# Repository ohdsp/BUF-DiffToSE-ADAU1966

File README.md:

# [Open Hardware DSP Platform](http://www.ohdsp.org)
## Differential to single ended buffer for ADAU1966 DAC
### Revision 1.1
###### BUF-DiffToSE-ADAU1966 (KiCad 4.0.2-stable)
---
# README
### Disclaimer
Copyright Paul Janicki 2016

Licensed under the TAPR Open Hardware License (www.tapr.org/OHL)

This documentation is distributed WITHOUT ANY EXPRESS OR IMPLIED WARRANTY, INCLUDING OF MERCHANTABILITY, SATISFACTORY QUALITY AND FITNESS FOR A PARTICULAR PURPOSE.

### What is this repository? ###

**Quick summary**

This is a differential to single ended active buffer for the ADAU1966 DAC. This is designed as part the Open Hardware DSP Platform. This may or may not be suitable for use in other applications. 

This repository contains the KiCad design files, manufacturing Gerber/drill files, and PDF/drawing files for this board.

### What is the project folder structure?
Most folder names are self explanatory. Starting from the top level: \
*BUF-DiffToSE-ADAU1966*
+ *Bill of Materials*  - This contains the bill of materials in CVS, LibreOffice Calc and XML formats
+ *Drawings*
    + *PCB* - This contains SVG and PDF outputs of PCB copper layers and assembly drawings
    + *Schematics* - This contains the PDF schematic drawing
+ *Gerbers* - This contains the PCB Gerbers and drill drawings for manufacture, there is also a zip file ready to send to most manufacturers
+ *KiCad* - This contains the original KiCad schematic and PCB design files

### How do I get set up? ###

**Summary of set up**

1. Set your self up a directory on a local disk, something simple will make life easier (eg C:\Electronics on Windows as used here), but anywhere will do just fine.
2. Download the Kicad-Libs from [https://github.com/ohdsp/KiCad-Libs](https://github.com/ohdsp/KiCad-Libs) and place in C:\Electronics\Kicad-Libs (or your chosen folder) 
3. Create a OHDSP subdirectory in C:\Electronics (so C:\Electronics\OHDSP)
3. Download this project to C:\Electronics\OHDSP\BUF-DiffToSE-ADAU1966
4. Fire up Kicad
5. Open the main project file C:\Electronics\OHDSP\BUF-DiffToSE-ADAU1966\Schematics\BUF-DiffToSE-ADAU1966.pro
6. (Optional) Setup Pcbnew component library as below.
7. Do as you wish with the project, just keep it under the TAPR Open Hardware License.

Make sure your git setup doesn't exclude files used in the project (like .LIB files) or things may go wrong down the line.

**KiCad Library Configuration**

Note that you need to setup a Pcbnew library, but the eeschema libraries should work without any changes if you followed the instructions above.

To setup Pcbnew libraries:

In Pcbnew go to Preferences -> Footprint Libraries Manager. Under Global Libraries tab in the top list check if there is a nickname "MyKiCadLibs-Footprints" (usually at the end of the list). If there is but it points to the wrong place then change the Library Path to point to MyKiCadLibs-Footprints (eg C:\Electronics\KiCad-Libs\MyKiCadLibs-Footprints.pretty) folder for your setup. If this is missing you can use "Append with Wizard", choose "Files on my computer", click next, browse to library location (eg C:\Electronics\KiCad-Libs\MyKiCadLibs-Footprints.pretty) and select the folder MyKiCadLibs-Footprints.pretty, click next, check the Status column states OK and the Format is KiCad (if not re-download the library) and click next, then select "To global library configuration..." and click Finish.

To setup eeschema component libraries:
Either from KiCad project window go to Tools -> Run Library Editor OR under eeschema, go to Tools -> Library Editor. Then Preferences -> Component Libraries.

The top section "Component Library Files" should ideally contain only two libraries, the "power" library that ships with KiCad and "MyKiCadLibs-Lib" available from above. To setup MyKiCadLibs-Lib as a relative path under the "User defined search path" click add. Browse to the location of KiCad-Libs you download above (eg C:\Electronics\KiCad-Libs) and click "Select Folder". Say yes to add a relative path. Under component library files click add, browse to the KiCad-libs again (eg C:\Electronics\KiCad-Libs), select file "MyKiCadLibs-Lib.lib" and click open. MyKiCadLibs-lib should appear in the component library list with no path as it will be using the user defined search path set in the box below.

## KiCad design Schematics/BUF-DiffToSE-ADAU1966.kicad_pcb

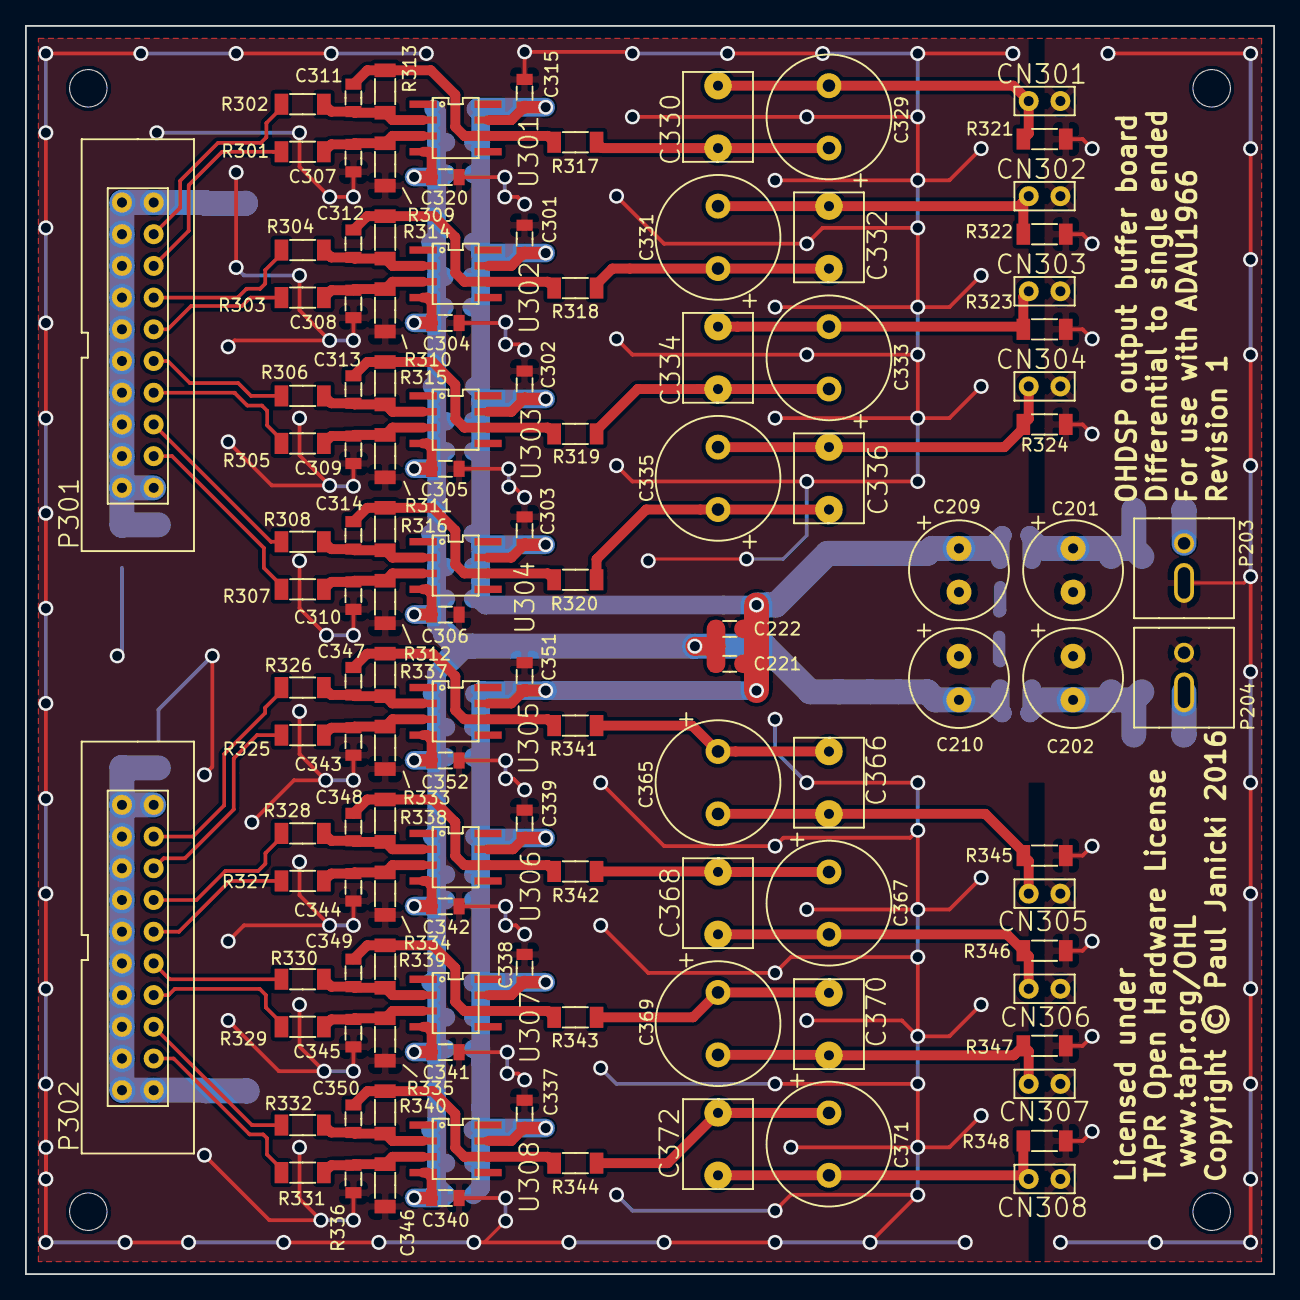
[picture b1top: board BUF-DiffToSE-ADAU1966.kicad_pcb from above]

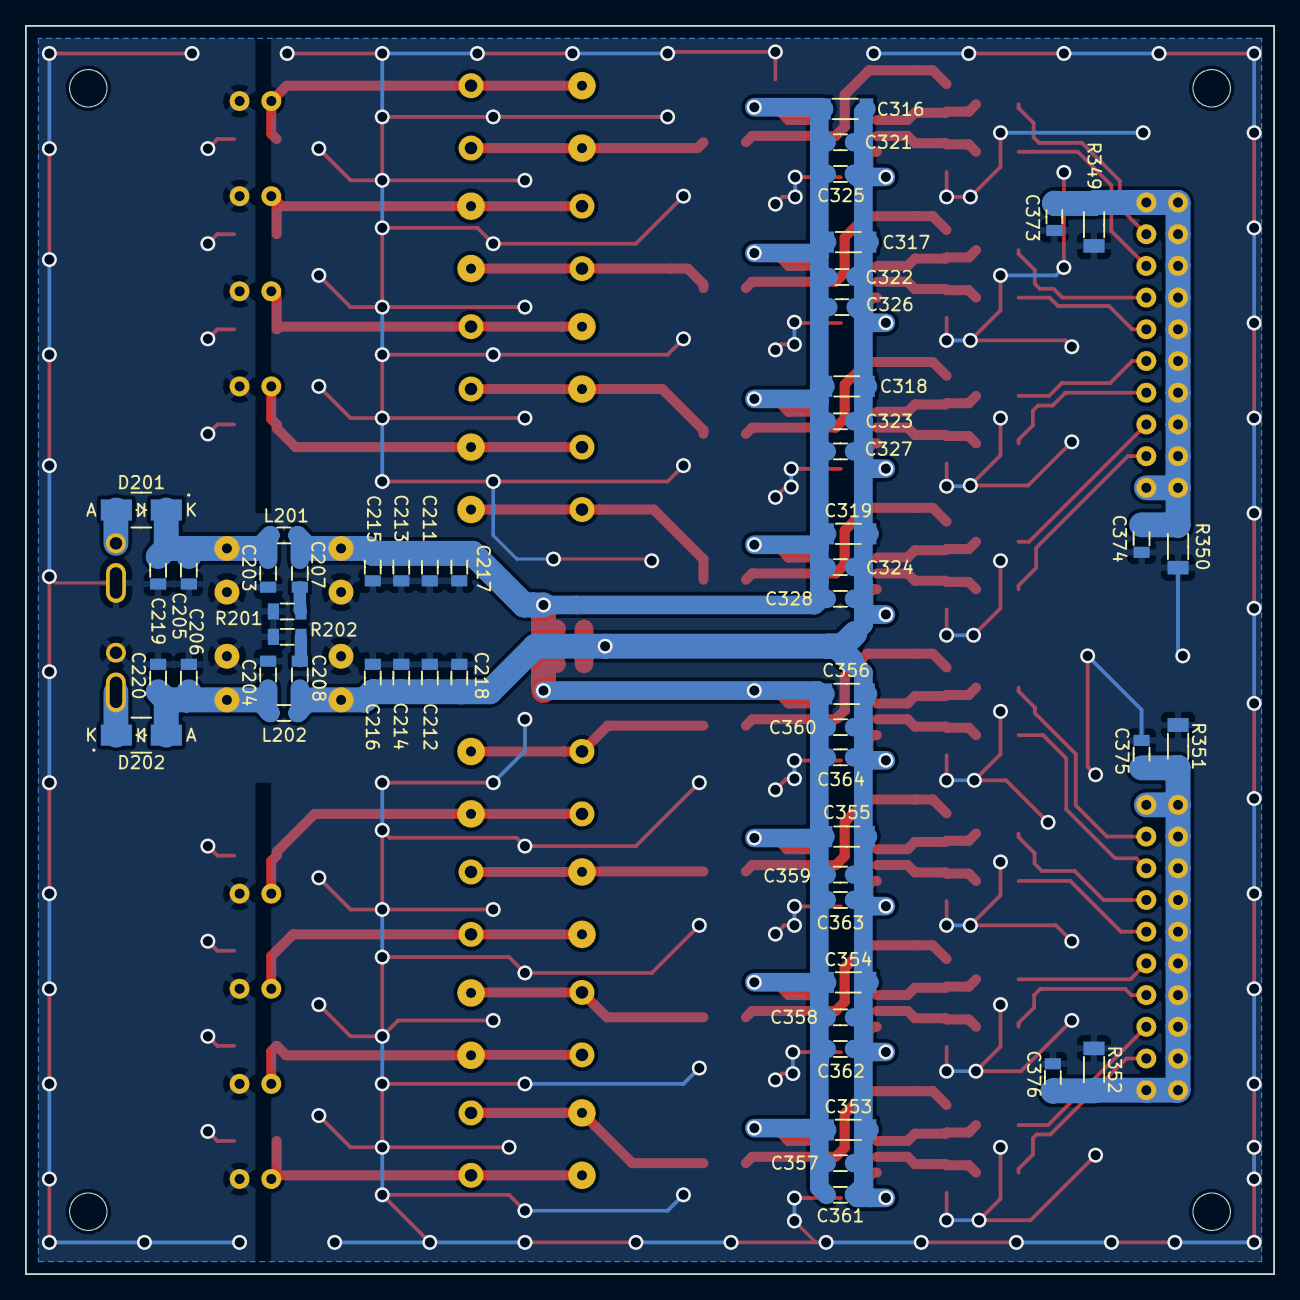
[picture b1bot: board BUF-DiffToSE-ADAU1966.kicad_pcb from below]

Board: 2 copper layers, 100.0 x 100.0 mm, 180 parts (54 on the bottom side), 67 nets.

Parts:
C201, C202, C209, C210: 220u; CAP-TH-D8mmP3.5mm
C203, C204, C211, C212, C222, C301, C302, C303, C304, C305, C306, C315, C320, C321, C322, C323, C324, C337, C338, C339, C340, C341, C342, C351, C352, C357, C358, C359, C360, C373, C374, C375, C376: 100n; SMD-0805
C205, C206, C213, C214, C325, C326, C327, C328, C361, C362, C363, C364: 10n; SMD-0805
C207, C208: 100p; SMD-0805
C215, C216, C307, C308, C309, C310, C311, C312, C313, C314, C343, C344, C345, C346, C347, C348, C349, C350: 1n; SMD-0805
C217, C218, C219, C220, C221: 22u; SMD-0805
C316, C317, C318, C319, C353, C354, C355, C356: 22u; SMD-1206
C329, C331, C333, C335, C365, C367, C369, C371: 100u; CAP-TH-D10mmP5mm
C330, C332, C334, C336, C366, C368, C370, C372: 100n; CAP_TH_5mm
CN301, CN302, CN303, CN304, CN305, CN306, CN307, CN308: COAX; CONN_SIL_2
D201, D202: B230A; DIODE-SMA
L201, L202: 600R@100MHz; SMD-0805
P201, P202, P205, P206: PIN; MountingHole_3mm
P203, P204: CONN_2x1; CONN-2WAY-2.54mm-3.81mm-SPACING
P301, P302: CONN_02X10; CONN_DIL_2X10_BOX
R201, R202: 47R; SMD-0805
R301, R302, R303, R304, R305, R306, R307, R308, R325, R326, R327, R328, R329, R330, R331, R332: 1k3; SMD-1206
R309, R310, R311, R312, R313, R314, R315, R316, R333, R334, R335, R336, R337, R338, R339, R340: 1k5; SMD-1206
R317, R318, R319, R320, R341, R342, R343, R344: 100; SMD-1206
R321, R322, R323, R324, R345, R346, R347, R348: 100K; SMD-1206
R349, R350, R351, R352: 10R; SMD-1206
U301, U302, U303, U304, U305, U306, U307, U308: IC-OPAMP-SINGLE-SOIC8; IC_SOIC_8

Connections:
+9VA: C207.1, C209.1, C211.1, C213.1, C215.1, C217.1, C221.1, C222.1, C301.1, C302.1, C303.1, C315.1, C316.1, C317.1, C318.1, C319.1, C321.1, C322.1, C323.1, C324.1, C325.1, C326.1, C327.1, C328.1, C337.1, C338.1, C339.1, C351.1, C353.1, C354.1, C355.1, C356.1, C357.1, C358.1, C359.1, C360.1, C361.1, C362.1, C363.1, C364.1, L201.2, U301.7, U302.7, U303.7, U304.7, U305.7, U306.7, U307.7, U308.7
-9VA: C208.2, C210.2, C212.2, C214.2, C216.2, C218.2, C221.2, C222.2, C304.2, C305.2, C306.2, C316.2, C317.2, C318.2, C319.2, C320.2, C321.2, C322.2, C323.2, C324.2, C325.2, C326.2, C327.2, C328.2, C340.2, C341.2, C342.2, C352.2, C353.2, C354.2, C355.2, C356.2, C357.2, C358.2, C359.2, C360.2, C361.2, C362.2, C363.2, C364.2, L202.2, U301.4, U302.4, U303.4, U304.4, U305.4, U306.4, U307.4, U308.4
GNDA: C201.2, C202.1, C203.2, C204.1, C205.2, C206.1, C209.2, C210.1, C211.2, C212.1, C213.2, C214.1, C215.2, C216.1, C217.2, C218.1, C219.2, C220.1, C301.2, C302.2, C303.2, C304.1, C305.1, C306.1, C307.2, C308.2, C309.2, C310.2, C315.2, C320.1, C337.2, C338.2, C339.2, C340.1, C341.1, C342.1, C343.2, C344.2, C345.2, C346.2, C351.2, C352.1, C373.2, C374.2, C375.2, C376.2, CN301.2, CN302.2, CN303.2, CN304.2, CN305.2, CN306.2, CN307.2, CN308.2, P203.2, P204.1, R201.2, R202.1, R309.1, R310.1, R311.1, R312.1, R321.1, R322.1, R323.1, R324.1, R333.1, R334.1, R335.1, R336.1, R345.1, R346.1, R347.1, R348.1, R349.1, R350.1, R351.1, R352.1
unnamed: C201.1, C203.1, C205.1, C219.1, D201.2, L201.1
unnamed: C202.2, C204.2, C206.2, C220.2, D202.1, L202.1
unnamed: C207.2, R201.1
unnamed: C208.1, R202.2
unnamed: C307.1, R301.1, R309.2, U301.3
unnamed: C308.1, R303.1, R310.2, U302.3
unnamed: C309.1, R305.1, R311.2, U303.3
unnamed: C310.1, R307.1, R312.2, U304.3
unnamed: C311.1, R302.1, R313.2, U301.2
unnamed: C311.2, R313.1, R317.2, U301.6
unnamed: C312.1, R304.1, R314.2, U302.2
unnamed: C312.2, R314.1, R318.2, U302.6
unnamed: C313.1, R306.1, R315.2, U303.2
unnamed: C313.2, R315.1, R319.2, U303.6
unnamed: C314.1, R308.1, R316.2, U304.2
unnamed: C314.2, R316.1, R320.2, U304.6
unnamed: C329.1, C330.1, R317.1
unnamed: C329.2, C330.2, CN301.1, R321.2
unnamed: C331.1, C332.1, R318.1
unnamed: C331.2, C332.2, CN302.1, R322.2
unnamed: C333.1, C334.1, R319.1
unnamed: C333.2, C334.2, CN303.1, R323.2
unnamed: C335.1, C336.1, R320.1
unnamed: C335.2, C336.2, CN304.1, R324.2
unnamed: C343.1, R325.1, R333.2, U305.3
unnamed: C344.1, R327.1, R334.2, U306.3
unnamed: C345.1, R329.1, R335.2, U307.3
unnamed: C346.1, R331.1, R336.2, U308.3
unnamed: C347.1, R326.1, R337.2, U305.2
unnamed: C347.2, R337.1, R341.2, U305.6
unnamed: C348.1, R328.1, R338.2, U306.2
unnamed: C348.2, R338.1, R342.2, U306.6
unnamed: C349.1, R330.1, R339.2, U307.2
unnamed: C349.2, R339.1, R343.2, U307.6
unnamed: C350.1, R332.1, R340.2, U308.2
unnamed: C350.2, R340.1, R344.2, U308.6
unnamed: C365.1, C366.1, R341.1
unnamed: C365.2, C366.2, CN305.1, R345.2
unnamed: C367.1, C368.1, R342.1
unnamed: C367.2, C368.2, CN306.1, R346.2
unnamed: C369.1, C370.1, R343.1
unnamed: C369.2, C370.2, CN307.1, R347.2
unnamed: C371.1, C372.1, R344.1
unnamed: C371.2, C372.2, CN308.1, R348.2
unnamed: C373.1, C374.1, P301.1, P301.2, P301.3, P301.5, P301.7, P301.9, P301.11, P301.13, P301.15, P301.17, P301.19, P301.20, R349.2, R350.2
unnamed: C375.1, C376.1, P302.1, P302.2, P302.3, P302.5, P302.7, P302.9, P302.11, P302.13, P302.15, P302.17, P302.19, P302.20, R351.2, R352.2
unnamed: D201.1, P203.1
unnamed: D202.2, P204.2
unnamed: P301.4, R302.2
unnamed: P301.6, R301.2
unnamed: P301.8, R304.2
unnamed: P301.10, R303.2
unnamed: P301.12, R306.2
unnamed: P301.14, R305.2
unnamed: P301.16, R308.2
unnamed: P301.18, R307.2
unnamed: P302.4, R326.2
unnamed: P302.6, R325.2
unnamed: P302.8, R328.2
unnamed: P302.10, R327.2
unnamed: P302.12, R330.2
unnamed: P302.14, R329.2
unnamed: P302.16, R332.2
unnamed: P302.18, R331.2

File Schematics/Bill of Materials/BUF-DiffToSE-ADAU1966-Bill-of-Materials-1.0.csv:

,"BUF-DiffToSE-ADAU1966 Bill of Materials Release 1.0",,,,,
,"24/01/16",,,,,
"Id","Designator","Package","Quantity","Designation","Detail",
1,"R202,R201","SMD-0805",2,"47R","100mW",
2,"C327,C326,C325,C205,C206,C213,C214,C328,C361,C362,C363,C364","SMD-0805",12,"10n","50V X7R 10%",
3,"C323,C322,C203,C204,C211,C212,C321,C324,C315,C320,C301,C302,C303,C304,C305,C306,C337,C338,C339,C340,C341,C342,C351,C352,C357,C358,C359,C360,C373,C374,C375,C376,C222","SMD-0805",33,"100n","50V X7R 10%",
4,"C314,C313,C311,C309,C308,C215,C216,C307,C310,C312,C343,C344,C345,C346,C347,C348,C349,C350","SMD-0805",18,"1n","50V X7R 10%",
5,"C201,C202,C209,C210","CAP-TH-D8mmP3.5mm",4,"220u","'=>35V eg Panasonic EEU-FC1V221L",
6,"C207,C208","SMD-0805",2,"100p","50V NP0 5%",
7,"C329,C331,C333,C335,C365,C367,C369,C371","CAP-TH-D10mmP5mm",8,"100u","'=>50V Panasonic EEUFC1H101 - In audio path",
8,"C330,C332,C334,C336,C366,C368,C370,C372","CAP_TH_5mm",8,"100n","63V 5mm Film Capacitor",
9,"CN301,CN302,CN303,CN304,CN305,CN306,CN307,CN308","CONN_SIL_2",8,"COAX","2.54mm pitch pin header or wire directly",
10,"D201,D202","DIODE-SMA",2,"B230A","Diodes Inc. B230A-13-F",
11,"L201,L202","SMD-0805",2,"600R@100MHz","'=>1A eg Wruth 742792040, TDK MPZ2012S601A",
12,"P201,P202,P205,P206","MountingHole_3mm",4,"PIN","Mounting hole only",
13,"P203,P204","CONN-2WAY-2.54mm-3.81mm-SPACING",2,"CONN_2x1","Any 2.54mm  or 3.81mm screw terminal eg CamdenBoss CTB0308/2",
14,"P301,P302","CONN_DIL_2X10_BOX",2,"CONN_02X10","2x10 2.54mm box header",
15,"R301,R302,R303,R304,R305,R306,R307,R308,R325,R326,R327,R328,R329,R330,R331,R332","SMD-1206",16,"1k3","MELF 0204",
16,"R309,R310,R311,R312,R313,R314,R315,R316,R333,R334,R335,R336,R337,R338,R339,R340","SMD-1206",16,"1k5","MELF 0204",
17,"R317,R318,R319,R320,R341,R342,R343,R344","SMD-1206",8,"100","MELF 0204",
18,"R321,R322,R323,R324,R345,R346,R347,R348","SMD-1206",8,"100K","MELF 0204",
19,"U301,U302,U303,U304,U305,U306,U307,U308","IC_SOIC_8",8,"IC-OPAMP-SINGLE-SOIC8","Texas Instruments OPA1641AID or low noise single op-amp",
20,"C316,C317,C318,C319,C353,C354,C355,C356","SMD-1206",8,"22u","35V X5R 20%",
21,"R349,R350,R351,R352","SMD-1206",4,"10R","MELF 0204",
22,"C217,C218,C219,C220,C221","SMD-0805",5,"22u","35V X5R 20%",

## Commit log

2016-01-24 Release 1.0
    Release 1.0
2016-05-25 Revision 2.0
2016-07-01 Revision 2.0
    Minor readme website link update
2016-07-01 Revision 2.0
    Update BOM sheet name

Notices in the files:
Schematics/BUF-DiffToSE-ADAU1966.kicad_pcb:
Copyright © Paul Janicki 2016
